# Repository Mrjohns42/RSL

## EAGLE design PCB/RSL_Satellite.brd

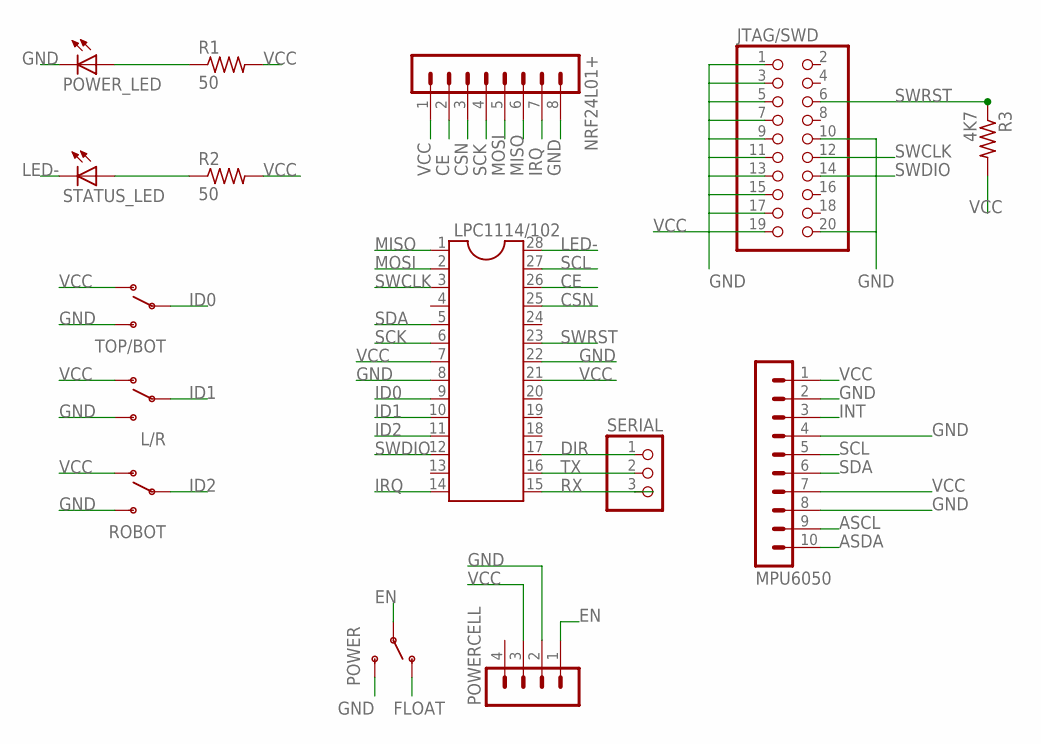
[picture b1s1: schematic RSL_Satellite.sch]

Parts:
JTAG/SWD: PINHD-2X10; 2X10
L/R: SWITCH-SPDTPTH; SWITCH-SPDT
LPC1114/102: DIL28; DIL28-6
MPU6050: MA10-1
NRF24L01+: MA08-1
POWER: SWITCH-SPDTPTH; SWITCH-SPDT
POWERCELL: MA04-1
POWER_LED: LED5MM
R1, R2: 50; 0207/10
R3: 4K7; 0207/10
ROBOT: SWITCH-SPDTPTH; SWITCH-SPDT
SERIAL: PINHD-1X3; 1X03
STATUS_LED: LED5MM
TOP/BOT: SWITCH-SPDTPTH; SWITCH-SPDT

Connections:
ASCL: MPU6050.9
ASDA: MPU6050.10
CE: LPC1114/102.26, NRF24L01+.2
CSN: LPC1114/102.25, NRF24L01+.3
DIR: LPC1114/102.17, SERIAL.1
EN: POWER.2, POWERCELL.1
FLOAT: POWER.1 (O)
GND: JTAG/SWD.1, JTAG/SWD.3, JTAG/SWD.5, JTAG/SWD.7, JTAG/SWD.9, JTAG/SWD.10, JTAG/SWD.11, JTAG/SWD.13, JTAG/SWD.15, JTAG/SWD.17, JTAG/SWD.20, L/R.3 (S), LPC1114/102.8, LPC1114/102.22, MPU6050.2, MPU6050.4, MPU6050.8, NRF24L01+.8, POWER.3 (S), POWERCELL.2, POWER_LED.K (C), ROBOT.3 (S), TOP/BOT.3 (S)
ID0: LPC1114/102.9, TOP/BOT.2
ID1: L/R.2, LPC1114/102.10
ID2: LPC1114/102.11, ROBOT.2
INT: MPU6050.3
IRQ: LPC1114/102.14, NRF24L01+.7
LED-: LPC1114/102.28, STATUS_LED.K (C)
MISO: LPC1114/102.1, NRF24L01+.6
MOSI: LPC1114/102.2, NRF24L01+.5
unnamed: POWER_LED.A, R1.1
unnamed: R2.1, STATUS_LED.A
RX: LPC1114/102.15, SERIAL.3
SCK: LPC1114/102.6, NRF24L01+.4
SCL: LPC1114/102.27, MPU6050.5
SDA: LPC1114/102.5, MPU6050.6
SWCLK: JTAG/SWD.12, LPC1114/102.3
SWDIO: JTAG/SWD.14, LPC1114/102.12
SWRST: JTAG/SWD.6, LPC1114/102.23, R3.1
TX: LPC1114/102.16, SERIAL.2
VCC: JTAG/SWD.19, L/R.1 (O), LPC1114/102.7, LPC1114/102.21, MPU6050.1, MPU6050.7, NRF24L01+.1, POWERCELL.3, R1.2, R2.2, R3.2, ROBOT.1 (O), TOP/BOT.1 (O)

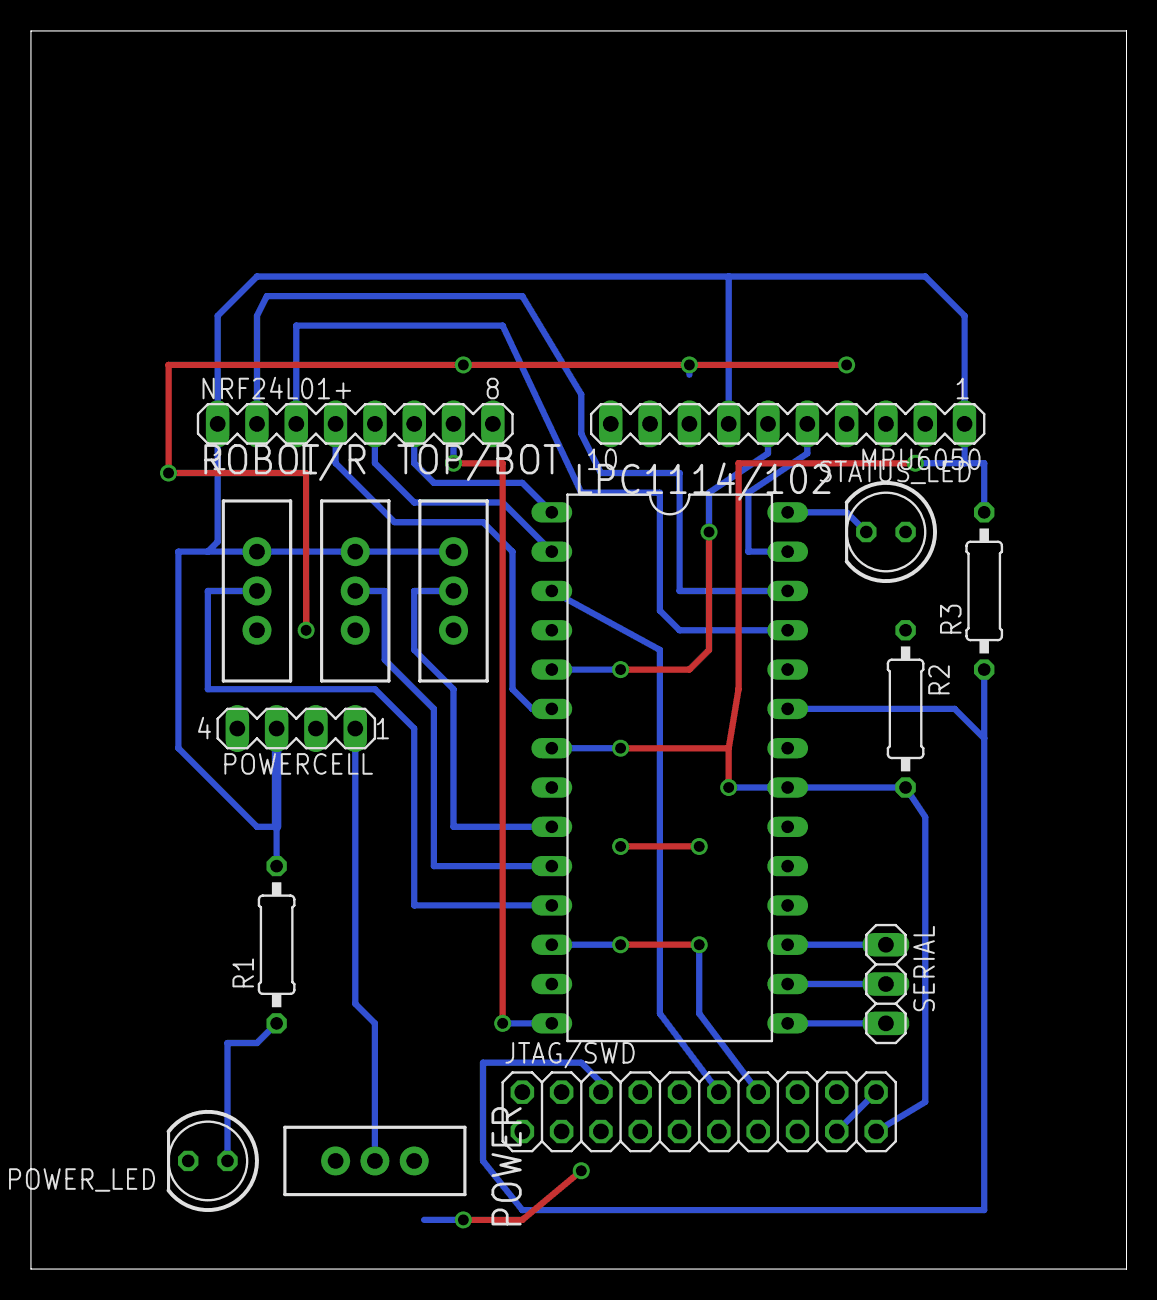
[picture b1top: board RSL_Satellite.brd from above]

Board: 2 copper layers, 70.8 x 80.0 mm, 15 parts (0 on the bottom side), 23 nets.

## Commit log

2013-02-12 better?
2013-02-12 it's good
2013-02-12 this is a nice message
2013-02-12 trying to merge servo and mpu code in RSL.ino
2013-02-13 RSL-polling works
2013-03-13 transceivers working
2013-03-13 2-way communication works
2013-04-19 Two way comm works with for loop delays.
2013-04-19 Stuff
2013-04-20 2 way comm works awesome
2013-04-30 DONE

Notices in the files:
parts and their libraries:
SparkFun-Electromechanical: Licensing: CC v3.0 Share-Alike You are welcome to use this library for commercial purposes.
